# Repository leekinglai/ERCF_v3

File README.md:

## Carrot Collective Projects

[ERCT / CottonTail Integrated Buffer](https://github.com/Carrot-collective/ERCT)

[Filametrix Toolhead Cutter](https://github.com/Carrot-collective/Filametrix)

[Blobifier Purge System](https://github.com/Carrot-collective/Blobifier)

[Filamentalist Rewinder Buffer](https://github.com/Carrot-collective/Filamentalist)

### Carrot Collective Affiliates

[Jabberwocky Toolhead](https://github.com/kinematicdigit/Jabberwocky)

[Happy Hare Wiki](https://github.com/moggieuk/Happy-Hare/wiki)

<br />

# Enraged Rabbit Community Project

<p align="center">
 
 <h1 align="center">ERCF v3.0</h1>
</p>

<p align="center">
An expandable MMU for Klipper-based 3D-Printers
</p>

<p align="center">
  &nbsp;
  &nbsp;
  &nbsp;
  &nbsp;
  &nbsp;
</p>

<br>

<table>
<tr>
<td width=30%></td>
<td>
This is a community-born project and a major update to the Voron ERCF MMU that was started a couple of years ago by Ette. It is endorsed by Ette, and the guiding philosophy wasn't to start again with a new MMU design but to refine what has already proven to be a very capable machine and push it to be the best it can be by simplifying problematic construction, improving reliability and aligning as close as possible to v2.0 BOM. The project includes an optional integrated filament buffer system (ERCT), filament cutter option (ERF), a collection of recommended tool head sensor modifications and a bit of Bling! It fully leverages the Happy Hare firmware MMU control software with Klipper Screen extensions.
<p>
 
There is a rapidly growing list of MMUs in the marketplace, from the mass-produced "Fords" who pioneered the market to the "Toyota" that are more recent efficient engineering feat but somehow lacked soul. We consider ERCFv3.0 the "BMW" - a little over-engineered perhaps but distinctively cool, and you feel good driving it. We hope you enjoy it!
</td>
</tr>
</table>

## Table of Content
 
**[ERCF](#enraged-rabbit-carrot-feeder-ercf)**<br>
**[ERCT](#-enraged-rabbit-cotton-tail-erct---filament-buffer)**<br>
**[ERF](#-toolhead-cutter-enraged-rabbit-filametrix-erf)**<br>
**[Toolhead Sensor Modifications](#-toolhead-cutter-enraged-rabbit-filametrix-erf)**<br>
**[Firmware](#firmware)**<br>
**[Documentation](#documentation)**<br>
**[BOM](#bom)**<br>
**[CAD](#cad)**<br>
**[FAQ](#faq)**<br>
**[Acknowledgements](#acknowledgements)**<br>
**[Vendors](#vendors)**<br>
**[Changelog](#changelog)**<br>
**[Build Photos](#build-photos)**<br>
**[Showroom](#user-print-showroom)**<br>
<!--
**[FAQ](Assets/FAQ.md)
-->

<br>

## Enraged Rabbit Carrot Feeder (ERCF)
<table>
<tr>
<td width=45%>An MMU or Multimaterial Unit/Upgrade allows for the automatic change of filaments on your 3D printer. You can use it to create beautiful multi-colored prints or, if you're lazy, simply to avoid loading filament by hand. If you are familiar with ERCF v1.1, this will serve as an overview of updates in v2:</td>
<td>
<ol>
 <li>Sturdy backbone - no more flex</li>
 <li>Reliable (and custom) encoder design</li>
 <li>Sprung servo instead of adjustable top hats</li>
 <li>Innovative Filament trap in blocks instead of magnetic gates</li>
 <li>Formal filament bypass</li>
 <li>Reinforced gearbox assembly</li>
 <li>Beautifully illustrated Manual</li></li>
 <li>High Quality Step-by-step CAD</li>
 <li>Integrated passive buffer system (Cotton Tail)</li>
 <li>Perfect tips with Filametrix Filament cutter</li>
 <li>Functional and aesthetic LED status indication</li>
</ol>
</td>
</tr>
</table>
New features in v3.0 include:
<ol>
 <li>New Direct Drive motor system optimized for torque and ease of use</li>
 <li>Redesigned Gearbox that supports legacy gearing options for upgraders</li>
 <li>Redesigned high-constraint filament blocks with pregate sensors as a default option</li>
 <li>Many Quality of Life additions such as improved Encoder and Selector Cart</li>
 <li>optional microswitch PCBs which allow solderless installation</li>
 <li>optional LED PCBs which allow solderless installation</li>
 <li>Detailed MMB v1.1 and v2.0 wiring diagrams</li>
 <li>Software Setup Documentation for the most popular boards</li>
 <li>Proper GitHub sections for User Mods, Mounting, and PCBs for the community to build upon</li>
 <li>Electronics boxes for the most popular boards: MMBv1 and v2, EasyBRD, ERB*</li>
</ol>

*The ERB is not recommended for use without an additional external 5v power supply.
<br>

## Optional Enraged Rabbit Components

The ERCF ecosystem includes several options to allow you to customize to your specific needs:

#### Filament Buffer/Rewinder Systems
When an MMU changes tool, the unloaded filament needs to be thoughtfully managed so that it doesn't tangle. The ERCF project provides two such systems. The best choice for you will depend on your specific setup:

<br>

###  Enraged Rabbit Cotton Tail (ERCT) - Filament Buffer
<table>
<tr>
<td width=30%></td>
<td>
The Enraged Rabbit Cotton Tail (ERCT) buffer system is designed to attach directly to ERCF v3.0. It is a passive system that optimizes space and is also designed to reduce resistance in the filament path, creating a consistent system for calibration.
<p>

ERCT includes a pre-gate filament sensor for automated filament loading and detect runout for endless spool feature. It also incorporates a NEOpixel on each gate that, when driven by the Happy Hare firmware, provides functional feedback and the necessary "bling!"
<p>

ERCT is a very compact and integrated buffer system that is great when your spools are remote from your printer.
<p>

[Read more](https://github.com/Carrot-collective/ERCT) &nbsp;&nbsp; Videos: [Rear Loading](https://youtu.be/9jzB5Un6HKo) [Front Loading](https://youtu.be/GlSXtUkd-b8)
</td>
</tr>
</table>

<br>

###  Enraged Rabbit Filamentalist - Filament Rewinder
<table>
<tr>
<td>
The Enraged Rabbit Filamentalist is an combined solution for buffering AND spool holder and thus provides total space savings. Rather than containing the unwound coils of filament it instead rewinds the filament back onto the spool which means there are never loose filament coils to tangle.
<p>

Filamentalist requires no additional motors because of its innovation of using the gear stepper of the MMU coupled through the filament to power both feeding and rewinding the spool. This can help overcome friction but caution is recommended for really soft TPU.
<p>

Filamentalist can also use the modular pre-gate filament sensor and gate entry LED blocks from ERCT so you don't give up on bling!
<p>

[Read more](https://github.com/Carrot-collective/Filamentalist)
</td>
<td width=30%></td>
</tr>
</table>

<br>

###  Toolhead Cutter: Enraged Rabbit Filametrix (ERF)
<table>
<tr>
<td width=30%></td>
<td>
Before the MMU can unload a filament, the tip must be prepared so that it can be cleanly loaded next time. This tip-forming process is very difficult to tune and varies based on material type, temperature, hotend type and even weather! Introducing Enraged Rabbit Filametrix (ERF) filament cutting system. This lightweight addition to your Stealthburner toolhead adds a cutting blade. When retracting, the problematic tip of the filament is simply cut off for perfect tips and no jams.
<p>

ERF also supports an optional servo operated ganrtry activation pin so no print area is lost with this addition. ERF designs also include the recommended integrated toolhead sensor
<p>

[Read more](https://github.com/Carrot-collective/Filametrix)
</td>
</tr>
</table>

<br>

###  Toolhead Sensor Modifications
<table>
<tr>
<td>
ERCF can be operated without a toolhead sensor (filament detection) in the toolhead but it is **not recommended**. A toolhead sensor provides an accurate homing point very close to the nozzle but also adds reliability to the tool change process. ERCF includes a set of toolhead sensor modifications for popular extruders. These work reliably through coupling a microswitch to the filament path.
<p>

[Read more](Recommended_Options/README.md)
</td>
</tr>
</table>

<br>

### Purge System (Blobifier)
<table>
<tr>
<td width=30%></td>
<td>

The Blobifier is a small device that eliminates the need for a purgeblock, making filament swaps quicker. It does this by extruding filament onto a tray creating a blob that will get ejected into a purge-bucket.<br />

<h3>Features</h3>

- Turn your filament purge into blobs for less waste and quicker purging.<br />
- Store the blobs in a bucket that can hold 400 blobs!<br />
- Automatically pause the printer once the bucket is full.<br />
- Detect when the bucket is installed or missing.<br />
- Shake the bucket for better dispersion of the blobs in the bucket.<br />
- Clean your nozzle on a brass brush before resuming to print.<br />

[Read More](https://github.com/Carrot-collective/Blobifier)

</td>
</tr>
</table>

<br>

## Firmware
<table>
<tr>
<td width=30%></td>
<td>
ERCF is designed to be used with the Happy Hare MMU firmware for Klipper which adds a set of klipper extensions for configuration setup, testing and operation of ERCF. These commands are available through the command line or macros but are perhaps best operated with an interactive UI with the optional KlipperScreen extension.
<p>

Happy Hare provides an easy installation script which has knowledge of recommended settings and will greatly accelerate the setup process.
<p>

[Happy Hare](https://github.com/moggieuk/Happy-Hare/wiki) &nbsp;&nbsp; [KlipperScreen HH Edition](https://github.com/moggieuk/KlipperScreen-Happy-Hare-Edition)
</td>
</tr>
</table>

<br>

## Documentation
<table>
<tr>
<td>
Building something as complex as an MMU is a challenging undertaking, but the ERCFv3.0 project contains an amazingly detailed and illustrated manual with step-by-step instructions. We have tried to make the process similar to fitting together a jigsaw puzzle, albeit with a few optional pieces.
<p>

[Documentation](Documentation)
[Get the latest version of the ERCFv3.0 PDF Manual](Documentation)
</td>
<td width=30%></td>
</tr>
</table>

<br>

## BOM
<table>
<tr>
<td width=30%></td>
<td>
You can find a Bill of Materials (BOM) and a convenient printed parts tracker for the project and options here. Note that the BOM also contains an upgrade list for those of you who want to use your existing ERCF v1.1 kits. Please make a copy and edit the "Filament Blocks #" to be the number of gates for your build. This can be any number, but we encourage kit vendors to use 4/8/12 as size variations. Note that there are separate columns for core ERCF, the optional ERCT and ERF options, as well as the suggested "extras"
<p>
Please be aware that the BOM is strictly for reference. The recommended parts can be exchanged for other similar quality parts. Manufacturers who use the BOM as a reference must submit an application for certification before selling them as ERCF v3.0 kits. Please contact us for certification.

[BOM](https://docs.google.com/spreadsheets/d/1UV0rU5Eo4hZX6hcIlSMzn-18oxGSBlLzFjurV6kf8oU/edit?usp=sharing) &nbsp;&nbsp; [Printed Parts Tracker](https://docs.google.com/spreadsheets/d/1MnmpiGlzxnq3sh8Gv73tNb6P1GbJ26OSJ0_e25pumdo/edit?usp=sharing)
</td>
</tr>
</table>

<br>

## CAD
<table>
<tr>
<td>
A lot of work has gone into creating a quality CAD model of the project, carefully organized into folders that match the documentation! It is highly recommended that you open the CAD and hide every folder and then expose them one at a time as you work through the build.
<p>

[Master CAD](CAD)
</td>
<td width=30%></td>
</tr>
</table>

<br>

## FAQ
ERCF v3 is currently at the fourth iteration or v3.0 phase. Design evolution has required some BOM changes over v2.0. We're sure there will be lots of questions. To avoid repetition on the various support channels, you can find a list of [frequently asked questions](FAQ.md) here. If something isn't answered the best place to go is the primary [ERCF Discord Server](https://discord.gg/t3STJC86HF)

<br>

## Acknowledgements
Most importantly let me introduce the development, test and doc team. A project like this doesn't happen without many hundreds of hours of volunteer effort and all of these folks are truely awesome. Please give some :clap: :clap: :clap:
<ul>
 <li>@Miriax (Designer & Doc Demon)
 <li>@kinematicdigit VS.744 (Designer & Vendor Relations)
 <li>@ningpj (Tester, Breaker & Documenter)
 <li>@SkiBikeMake (Mr Filamentalist)
 <li>@moggieuk V0.1503 | v3.4088 (Mr Happy Hare)
 <li>@gneu v3.0345 (Filament block & bling innovator)
 <li>@sneakytreesnake v3.3804 (The project backbone!)
 <li>@mneuhaus VT.483 (Mr Binky)
 <li>@fizzy (King of CAD)
 <li>@gsx8299 (Test Builder Extraordinaire)
 <li>@sorted (Filametrix "don't get enraged" filament cutting system)
 <li>@kierantheman (Mr ThumperBlocks)
 <li>@Fragmon (Videographer)
 <li>@Silverback v3.1356 (Filametrix tester, builder & engineer)
</ul>

<br>

## Vendors
<table>
<tr>
<td width=25%></td>
<td>
These kits and specialty parts will have been checked by us and meet good quality standards. Pending Certification means it has met our first pass inspection and in the process of being verified as a v3 kit. <strong>WE DO NOT RECOMMEND PURCHASING KITS WITHOUT THE CERTIFICATION BY US. PLEASE CHECK BACK HERE FOR THE LIST OF AUTHORIZED VENDORS AND MANUFACTURERS</strong>:<br>
<p>
<ul>
 <li> Approved - Siboor
 </li>
 <li> Pending Submission - Triangle Labs
 </li>
 <li> Approved - <a href="https://www.aliexpress.us/item/3256810002191161.html">Seleadlabs</a>
 </li>
 <li> Pending Submission - Makerpanda
 </li>
 <li> Pending Submission - Fysetc
 </li>
 <li> Approved - <a href="https://www.aliexpress.com/item/1005010543365831.html">Vano3dla 8 channel</a> <a href="https://www.aliexpress.com/item/1005011827763626.html">12 channel</a>
 </li>

 <br>
 <p>
 A list of more official and certified vendors is on the way... stay tuned!
</td>
</tr>
</table>

**Manufacturers:**
_If you want to be included, please contact us. We are happy to validate your kit/parts and then add you to the list._

<br>

## Changelog
<ul>
 <li>v3.0 - Full Release</li>
 <li>v2.0 - Full Release (Happy Easter!)
 <li>v2 RC1 - Initial Release (Happy Christmas!)
</ul>

CAD Design Guidelines used in this project (in case you were interested) can be found: [here](/Assets/Dev_Notes.md).

<hr>

<p align="center"><i>
There once was a printer so keen,<br>
To print in red, yellow, and green.<br>
It whirred and it spun,<br>
Mixing colors for fun,<br>
The most vibrant prints ever seen!
</i></p>

<br>

## Build Photos

Click to enlarge.

<br>

## User Print Showroom

Click to enlarge.

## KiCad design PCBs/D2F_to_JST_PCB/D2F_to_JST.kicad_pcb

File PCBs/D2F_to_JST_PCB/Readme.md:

## D2F to JST PCB

Design by TheRogueZeta.

## Instructions

First, remove the middle leg of the D2F microswitch. Cut or file it down as close to flush with the D2F microswitch body as possible, as any remaining leg will interfere with the PCB.

Next, solder the JST connector to the PCB. PH (2.0mm), XH (2.5mm) or 2.54mm connectors all fit. Once cool, trim the protruding legs of the JST connector. You want them as close to flush as you can get without damaging the solder joint.

Next, add a printed shim or Kapton tape to the microswitch to prevent shorting the middle leg of the D2F microswitch on the JST connector.

Finally, solder the microswitch to the PCB as flush as possible.

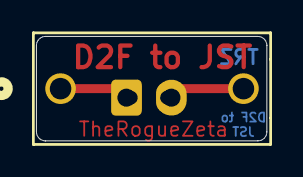
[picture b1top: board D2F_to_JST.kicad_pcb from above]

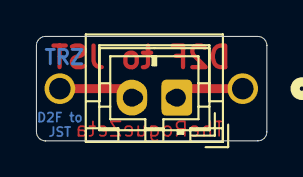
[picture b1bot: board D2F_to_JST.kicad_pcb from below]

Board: 2 copper layers, 12.8 x 5.8 mm, 3 parts (2 on the bottom side), 2 nets.

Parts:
J1: Conn_01x02_Pin; JST_XH_B2B-XH-A_1x02_P2.50mm_Vertical
J2: Conn_01x02_Pin; JST_PH_B2B-PH-K_1x02_P2.00mm_Vertical
SW1: SW_SPDT; D2F

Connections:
unnamed: J1.1, J2.1, SW1.1 (A)
unnamed: J1.2, J2.2, SW1.3 (C)

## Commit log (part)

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2025-02-15 Update README.md
    Change RC2 to v2.5
2025-02-23 Update QuickStart.md
    Fixed a few links
2025-02-27 Reorganization and Renaming
    Reorganized and renamed files. Added new versions of Motor Mounts, Gearbox, and Gearbox LED.
2025-03-06 Added copies of Happy Hare documentation
    Copied the necessary setup pages from the Happy Hare wiki. Started to make them ERCF-flavored, but there's a lot more to do.
2025-03-06 Fixed more links
    Fixed more links
2025-03-06 Added local images
    Added local images and fixed links to those images.
2025-03-07 Cleanup
2025-03-07 Add pictures
2025-03-08 Decided to Rewrite Everything
    I'm going to rewrite everything, the source information overlaps too much.
2025-03-08 Fixed links and edited to be ERCF-Specific
    Fixed image links, links to Happy Hare docs, and made the language ERCF-Specific.
2025-03-08 Update Happy Hare Install page
    Added new images, tweaked verbiage.
2025-03-09 Update STLs for Printing Orientation
    Update STLs for Printing Orientation
2025-03-09 Renamed "Calibrating Your Hardware"
    "Hardware Configuration Checks" is much more accurate
2025-03-09 Update Gearbox_v6.stl
    Added the supports back in.
2025-03-09 Update Hardware-Calibration.md
    Edits round 1 / ??
2025-03-10 Top hat with correct print support
2025-03-10 Update Hardware-Calibration.md
    Fixed another link.
2025-03-10 Update Installing-KlipperScreen.md
    Rewrites 1 / ??
2025-03-10 Cleanup and Tying it All Together
    Cleaned up old doc pages. Fixed the links at the bottom of every page. Should be 95% done now.
2025-03-10 Delete [a]_Selector_Cart_v2.8.stl
    Remove version with bad supports
2025-03-10 New PTFE Tool
    Renamed the previous tool to disambiguate
2025-03-11 Renamed Runout Buffer Coupler Block
    It needed to have the _xN suffix.
2025-03-11 Update Hardware-Calibration.md
    Added the "add the servo arm" step, that's slightly important
2025-03-11 Update Hardware-Calibration.md
    wording
2025-03-11 Update Hardware-configuration-checks.md
    Phrasing
2025-03-11 Create Base_v03.stl
    Quick fix for the MMBv2 base
2025-03-11 Create [a]_Selector_Cart_v2.82.stl
    Thanks to Igiannakas for the mods!
2025-03-12 Update LED_Diffuser_v3.stl
    Reoriented for printing
2025-03-13 Renamed folders and add ERCT V3 CAD
2025-03-13 Update Logo_Mask_v32.stl
    Fixed print orientation
2025-03-13 Create Linear_Axis_Idler_Block_10mm_v2.stl
    Removed added thickness from bolt path
2025-03-14 Update Hardware-Calibration.md
    Small verbiage update
2025-03-14 Reorganize and delete extra files
2025-03-14 Update Flashing-Local-MCU.md
    Details!
2025-03-14 Update Flashing-Local-MCU.md
    Last formatting update (I think)
2025-03-14 Update Flashing-Local-MCU.md
    Yet more formatting
2025-03-14 Additional Axle for 9 and 12
    9, 12 and segmented 12 gate axles added.
2025-03-15 Create Toolhead-Distances.md
    Forgot a page! Links to be fixed soon
2025-03-15 Fix links and add images for Toolhead Distances page
2025-03-15 Tweaks for Toolhead Distances
    Small verbiage tweaks.
2025-03-15 Small updates
    notes about how the servo down command deliberately makes the Gear motor twitch.
2025-03-17 Add printable cable chain
2025-03-19 Printable Cable Chain Updates
    Updated printable cable chain files to be shorter. Added middle section and 3MF files.
2025-03-20 Create ERCFv2.5_Manual_03-20-25.pdf
    Textual updates, no graphical updates yet.
2025-03-21 Remove old versions of files
2025-03-25 Create Logo_Mask_v33.stl
    Another try at better support.
2025-03-27 Experimental 9.4 Blocks
2025-03-29 Update Hardware Calibration
    Fixed a typo and some verbiage in the MMU_CALIBRATE_BOWDEN section
2025-03-31 Update Happy-Hare-Configuration.md
    Updated example gcode
2025-04-05 Create [a]_Selector_Cart_v2.812.stl
    Added the Springy viewport.
2025-04-05 New COAS mount
    New version of the COAS mount for front-facing ERCFs.
2025-04-05 New MultiMaterial Test
    Organized the part labels.
2025-04-06 Filament Path Block 9.7
    Two versions available, Magnetic Switch, and without.
2025-04-09 Create [a]_Selector_Cart_v2.9.stl
    Moved the belt path over 0.55m for perfect alignment.
2025-04-09 Update [a]_Selector_Cart_v2.9.stl
    Fix print orientation
2025-04-12 Split Coupler Cleanup and New B Version
    -removed the unisolated couplers
    -Added v2, with 7mm diameter hole for an M3 washer
2025-04-12 Update Filament_path_C9.8BL_xN.stl
    Added Print support
2025-04-15 Create [a]_Customizable_Split_Coupler_B.3mf
    Customizable Split Coupler created for shaft flat depths at 4.0, 4.1, 4.2, 4.3, 4.4, and 4.5mm (default).
2025-04-15 Create [a]_Gear_Box_Top_Panel_v2.stl
    Cosmetic update for the Top_Panel to add alignment arrows.
2025-04-16 Create ERCF_V2.5_v60.f3d
    Newest CAD with Filament_Path C9.8
2025-04-17 Updated Base and Brakes
    Updated the Base to align the Brakes better, move the version number, alignment line, and printability improvements.
    Updated the Filament Trap and Filament Brake to center the mounting hole and make it fit better generally.
2025-04-19 Clean up Tools Folder
    Removed old files that are no longer needed.
2025-04-19 Cleanup Selector Folder
    Removed old files that aren't needed anymore.
2025-04-19 Update Linear_Axis_Selector_Motor_Support_Precise_v2.stl
    Fixed printing orientation.
2025-04-19 New Filament Path C9.9
    New Filament Path C9.9 with refreshed CAD.
2025-04-19 Create ERCF_V2.5_v66.f3d
    Even newer CAD!
    -added new COAS mounts
    -added MMBv2 mount update with hinge
    -Colormatched a few things
    -switched to microswitch filament paths
2025-04-20 9 Gate Axle
2025-04-25 Create ERCFv2.5_Manual_04-25-25.pdf
    New Manual edition with newly replace images
2025-04-25 Encoder Updates
    8-Toothed Wheel
    Added chamfer and updated version number of Encoders
2025-04-25 Rename Filament Path Parts
    They are accent colored now.
2025-04-26 Create ERCFv2.5_Manual_04-26-25.pdf
    New manual. Better belt installation pages, added lots of small details, added wiring page links, lots of typos fixed.
2025-04-29 Reorganize Filament Block Files
    Rearranged the Filament Block files to integrate the new version, and move the old versions to Legacy folders.
2025-04-30 Update Buffer Wall Inlet
2025-04-30 Flatten Runout Buffer Folder Structure
    Removed unnecessary folder.
2025-04-30 Runout Buffer -> CottonTail Lite
    Calling it what the people have dubbed it!
2025-05-04 New Tools and Torture Test
    New Calibration piece with updated filament path and overhang tests.
    New color changing spiral torture test.
2025-05-04 Alpha MMBv1 Box
    Alpha files for the MMBv1 box
2025-05-04 Create MMB_mount_hinge.stl
    Missed a file!
2025-05-04 Update Base_C10_U5_xN.stl
    Print support for Base
2025-05-04 MMBv2 Box Updates
    Updates to MMBv2 box.
2025-05-04 ERB and EASY_BRD Boxes
    Initial files for ERB and EASY_BRD boxes.
2025-05-04 Update ERB_Box_Lid_v01.stl
    Flipped to print orientation
2025-05-05 Create Base_C10_U5_xN_M2_PIN.stl
    BASE Version for M2 18 mm or 20 mm steel pin.
2025-05-06 v2 of ERB Electronics Box
    -Added 0.25mm of clearance so that the board doesn't strain when removed
    -Added 4mm of height to the lid to clear the stepper driver heatsinks
    -Thickened the lid mesh from 0.6mm to 1.0mm to make it sturdier
2025-05-06 ignore .ds
2025-05-06 Ignore
    Ignore
2025-05-07 Update Filament_Block_C10_R3_xN.stl
    Added Arrow to block
2025-05-10 New versions
    Updated versions with small tweaks. Fixed the Revo Front to have the Filametrix mods.
2025-05-11 C10 Rev 4
    C10 Revision 4
    Change Log
    Base Block - Recommended replaced from Rev 3
    - Removed 2020 Indexing part and replaced with sidewalls. This should make it compatible with any 2020 Extrusion and any compatible Roll-in T-Nuts.
    - Added partial printed threading for hinge. Can accept either M3x20 SHCS or Pin
    Top Hat - Cosmetic/printability improvements not required replacement for Rev 3
2025-05-11 Encoder v25B_R2
    Revision 2 update. Added bevels to give it more clearance and move across blocks.
2025-05-13 Update Encoder_Left_v25B_R2_M5.stl
    adjusted tolerance
2025-05-16 Create MMBv2_Box_Lid_v04.stl
    Re-added hinges to Lid
2025-05-18 Encoder v25B Revision2
2025-05-22 Update ERB Electronics Box
    -Increased lid height to clear heatsinks
    -Removed material from lid to clear USB port
    -Increased base pin recess depth
2025-06-13 Update ERB_Box_Base_v03.stl
    Replace with correct file
2025-06-21 Filament Block C10_Revision 5
2025-07-03 Updated Filament Path
2025-07-08 New Filament Path variants
    Uploaded to Github late
2025-07-09 Updates to Filament Blocks
2025-07-14 Filament Block Revision
2025-07-14 Filament Path R7
    Filament Path R7 with corrected switch, MR85zz bearing, and printed lever cavities.
2025-07-27 Swap Brake Options
    The Brakeless option is now the main option
2025-07-29 Update to Fiilament Blocks
    Fixed 120-degree opening feature
2025-08-02 R7 Tophat, brake and latch.
2025-08-06 Rename
    I swapped the names, whoops
2025-08-16 Cleanup old files
    Cleanup of old files
2025-08-16 Cleanup ERCT v2 Archive
2025-08-23 V26B Encoder
    Updated version of the Encoder
2025-08-30 Update Filament_Path_C10D_R10.stl
    Fixed the supports that Fusion broke.
2025-08-30 Copy in Latest Filamentalist Files
    Copied in the latest Filamentalist files.
2025-09-06 New STL versions
2025-09-09 Old files cleanup
    Cleanup old / legacy files.
2025-09-09 Mount STLs
2025-09-10 New M6 Options
    Added BHCS option, STEP files, Readme
2025-09-10 Flipped Motor Support to User Mod Standards
2025-09-12 Add Metal Coupler Sleeve
    Initial commit
2025-09-12 Update readme.md
    Really fix the image links this time
2025-09-12 Update README.md
    Added Metal Coupler Sleeve
2025-09-17 Create PCB Folder
2025-09-17 Spelling fixes
2025-10-06 Cleanup old versions
2025-10-10 Cleanup CAD folder
2025-10-10 Latest CAD
2025-10-10 Rename STLs Folder (2)
2025-10-11 Cleanup ERCT files to new Repo
2025-10-12 Fix graphics
2025-10-12 Move Filament Path STEP file
2025-10-18 Update Servo Sleds
    Update to correct orientation with supports
2025-10-23 Fix Filenames
2025-10-26 Rename Legacy Geared Manual
    Renamed the file for clarity, and to put the main manual first in the folder.
2025-11-12 Update README.md
    Update Discord link
2026-04-10 Update README.md
    Fixed vendor links
